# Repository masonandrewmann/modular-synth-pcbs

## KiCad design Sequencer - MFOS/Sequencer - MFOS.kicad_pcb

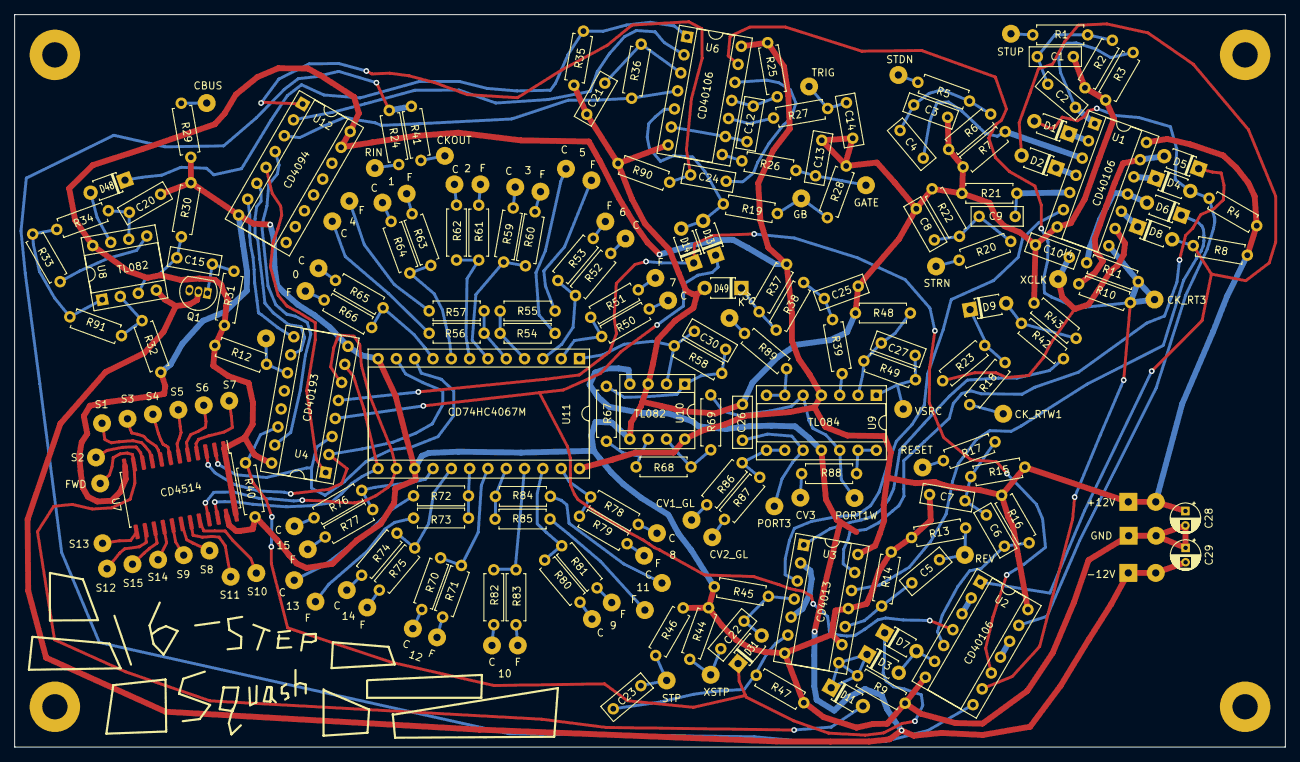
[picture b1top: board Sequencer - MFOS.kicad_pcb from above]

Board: 2 copper layers, 176.3 x 101.6 mm, 219 parts (0 on the bottom side), 162 nets.

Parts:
C1, C3, C7, C8, C22, C23: 0.01uF; C_Rect_L7.0mm_W2.5mm_P5.00mm
C2, C4, C5, C6, C9: 0.02uF; C_Rect_L7.0mm_W2.5mm_P5.00mm
C10: 1uF; C_Rect_L7.0mm_W2.5mm_P5.00mm
C12, C13, C14, C21: 0.001u; C_Rect_L7.0mm_W2.5mm_P5.00mm
C15, C20: 0.01u; C_Rect_L7.0mm_W2.5mm_P5.00mm
C24: 100p; C_Rect_L7.0mm_W2.5mm_P5.00mm
C25, C26: 0.1u; C_Rect_L7.0mm_W2.5mm_P5.00mm
C27, C30: 470p; C_Rect_L7.0mm_W2.5mm_P5.00mm
C28, C29: 100u; CP_Radial_D4.0mm_P2.00mm
D1, D2, D3, D4, D5, D6, D7, D8, D9, D11, D13, D14, D31, D48: D; D_T-1_P5.08mm_Horizontal
D49: D_Zener; D_T-1_P5.08mm_Horizontal
J1: STUP; SolderWirePad_1x01_Drill1mm
J2: STDN; SolderWirePad_1x01_Drill1mm
J3: XSTP; SolderWirePad_1x01_Drill1mm
J4: XCLK; SolderWirePad_1x01_Drill1mm
J5: CKOUT; SolderWirePad_1x01_Drill1mm
J6: GATE; SolderWirePad_1x01_Drill1mm
J7: TRIG; SolderWirePad_1x01_Drill1mm
J8: GB; SolderWirePad_1x01_Drill1mm
J9: CBUS; SolderWirePad_1x01_Drill1mm
J10: S7; SolderWirePad_1x01_Drill1mm
J11: S6; SolderWirePad_1x01_Drill1mm
J12: S5; SolderWirePad_1x01_Drill1mm
J13: S4; SolderWirePad_1x01_Drill1mm
J14: S3; SolderWirePad_1x01_Drill1mm
J15: S2; SolderWirePad_1x01_Drill1mm
J16: S1; SolderWirePad_1x01_Drill1mm
J17: S0; SolderWirePad_1x01_Drill1mm
J18: S8; SolderWirePad_1x01_Drill1mm
J19: S9; SolderWirePad_1x01_Drill1mm
J20: S10; SolderWirePad_1x01_Drill1mm
J21: S11; SolderWirePad_1x01_Drill1mm
J22: RIN; SolderWirePad_1x01_Drill1mm
J23: S12; SolderWirePad_1x01_Drill1mm
J24: S13; SolderWirePad_1x01_Drill1mm
J25: S14; SolderWirePad_1x01_Drill1mm
J26: S15; SolderWirePad_1x01_Drill1mm
J27: CV1_GL; SolderWirePad_1x01_Drill1mm
J28: CV2_GL; SolderWirePad_1x01_Drill1mm
J29: CV3; SolderWirePad_1x01_Drill1mm
J30: CV4; SolderWirePad_1x01_Drill1mm
J31: 7C; SolderWirePad_1x01_Drill1mm
J32: 7F; SolderWirePad_1x01_Drill1mm
J33: 6C; SolderWirePad_1x01_Drill1mm
J34: 6F; SolderWirePad_1x01_Drill1mm
J35: 5C; SolderWirePad_1x01_Drill1mm
J36: 5F; SolderWirePad_1x01_Drill1mm
J37: 4C; SolderWirePad_1x01_Drill1mm
J38: 4F; SolderWirePad_1x01_Drill1mm
J39: 3C; SolderWirePad_1x01_Drill1mm
J40: 3F; SolderWirePad_1x01_Drill1mm
J41: 2C; SolderWirePad_1x01_Drill1mm
J42: 2F; SolderWirePad_1x01_Drill1mm
J43: 1C; SolderWirePad_1x01_Drill1mm
J44: 1F; SolderWirePad_1x01_Drill1mm
J45: 0C; SolderWirePad_1x01_Drill1mm
J46: 0F; SolderWirePad_1x01_Drill1mm
J47: 12C; SolderWirePad_1x01_Drill1mm
J48: 12F; SolderWirePad_1x01_Drill1mm
J49: 13C; SolderWirePad_1x01_Drill1mm
J50: 13F; SolderWirePad_1x01_Drill1mm
J51: 14C; SolderWirePad_1x01_Drill1mm
J52: 14F; SolderWirePad_1x01_Drill1mm
J53: 15C; SolderWirePad_1x01_Drill1mm
J54: 15F; SolderWirePad_1x01_Drill1mm
J55: 8C; SolderWirePad_1x01_Drill1mm
J56: 8F; SolderWirePad_1x01_Drill1mm
J57: 9C; SolderWirePad_1x01_Drill1mm
J58: 9F; SolderWirePad_1x01_Drill1mm
J59: 10C; SolderWirePad_1x01_Drill1mm
J60: 10F; SolderWirePad_1x01_Drill1mm
J61: 11C; SolderWirePad_1x01_Drill1mm
J62: 11F; SolderWirePad_1x01_Drill1mm
J63: CK_RT1W; SolderWirePad_1x01_Drill1mm
J64: CK_RT3; SolderWirePad_1x01_Drill1mm
J65: STRN; SolderWirePad_1x01_Drill1mm
J66: REV; SolderWirePad_1x01_Drill1mm
J67: STP; SolderWirePad_1x01_Drill1mm
J68: RESET; SolderWirePad_1x01_Drill1mm
J69: RAND; SolderWirePad_1x01_Drill1mm
J70: PORT1W; SolderWirePad_1x01_Drill1mm
J71: PORT3; SolderWirePad_1x01_Drill1mm
J72: VSRC; SolderWirePad_1x01_Drill1mm
J73: +12V_Conn; SolderWirePad_1x02_P3.81mm_Drill1mm
J74: GND_Conn; SolderWirePad_1x02_P3.81mm_Drill1mm
J75: -12V_Conn; SolderWirePad_1x02_P3.81mm_Drill1mm
Q1: 2N3904; TO-92_Inline
R1, R5, R10, R11, R17, R20, R90: 10K; R_Axial_DIN0207_L6.3mm_D2.5mm_P7.62mm_Horizontal
R2, R6, R15, R22: 680K; R_Axial_DIN0207_L6.3mm_D2.5mm_P7.62mm_Horizontal
R3, R7, R16, R21: 220K; R_Axial_DIN0207_L6.3mm_D2.5mm_P7.62mm_Horizontal
R4, R8, R12, R40: 47K; R_Axial_DIN0207_L6.3mm_D2.5mm_P7.62mm_Horizontal
R9, R19, R33, R44, R45, R46, R47, R50, R52, R54, R56, R59, R61, R63, R65, R70, R72, R74, R76, R78, R80, R82, R84: 100K; R_Axial_DIN0207_L6.3mm_D2.5mm_P7.62mm_Horizontal
R13, R14, R34, R36: 1M; R_Axial_DIN0207_L6.3mm_D2.5mm_P7.62mm_Horizontal
R18: 20K; R_Axial_DIN0207_L6.3mm_D2.5mm_P7.62mm_Horizontal
R23: 6.2K; R_Axial_DIN0207_L6.3mm_D2.5mm_P7.62mm_Horizontal
R24: 3K; R_Axial_DIN0207_L6.3mm_D2.5mm_P7.62mm_Horizontal
R25, R48, R58: 100k; R_Axial_DIN0207_L6.3mm_D2.5mm_P7.62mm_Horizontal
R26, R27, R86, R87, R88, R89: 1k; R_Axial_DIN0207_L6.3mm_D2.5mm_P7.62mm_Horizontal
R28, R32, R35: 4k7; R_Axial_DIN0207_L6.3mm_D2.5mm_P7.62mm_Horizontal
R29: 3k; R_Axial_DIN0207_L6.3mm_D2.5mm_P7.62mm_Horizontal
R30, R31, R51, R53, R55, R57, R60, R62, R64, R66, R71, R73, R75, R77, R79, R81, R83, R85: 2M; R_Axial_DIN0207_L6.3mm_D2.5mm_P7.62mm_Horizontal
R37, R67, R68: 10k; R_Axial_DIN0207_L6.3mm_D2.5mm_P7.62mm_Horizontal
R38, R39: 47k; R_Axial_DIN0207_L6.3mm_D2.5mm_P7.62mm_Horizontal
R41, R42: 1K; R_Axial_DIN0207_L6.3mm_D2.5mm_P7.62mm_Horizontal
R43: 3.9K; R_Axial_DIN0207_L6.3mm_D2.5mm_P7.62mm_Horizontal
R49: 200k; R_Axial_DIN0207_L6.3mm_D2.5mm_P7.62mm_Horizontal
R69: 22; R_Axial_DIN0207_L6.3mm_D2.5mm_P7.62mm_Horizontal
R91: 4M7; R_Axial_DIN0207_L6.3mm_D2.5mm_P7.62mm_Horizontal
U1, U2, U6: 40106; DIP-14_W7.62mm_Socket
U3: 4013; DIP-14_W7.62mm_Socket
U4: 40193; DIP-16_W7.62mm_Socket
U7: 4514; SOIC-24W_7.5x15.4mm_P1.27mm
U8, U10: TL082; DIP-8_W7.62mm_Socket
U9: TL084; DIP-14_W7.62mm_Socket
U11: CD74HC4067M; DIP-24_W15.24mm_Socket
U12: CD4094; DIP-16_W7.62mm_Socket
e: MountingHole_3.5mm_Pad

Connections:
+12V: C28.1, J73.1, J73.2, R4.2, R8.2, R12.1, R15.2, R16.1, R25.2, R31.1, R37.2, U1.14, U2.14, U3.14, U4.16, U6.14, U7.1, U7.24, U8.8, U9.4, U10.8, U11.24, U12.15, U12.16
-12V: C29.2, J75.1, J75.2, Q1.2, U8.4, U9.11, U10.4
CLK: J64.1, R10.2, R11.2, U1.8, U2.9, U6.13
CLR: D7.1, D31.1, R40.1, U4.14
DA: U4.15, U12.4
DB: U4.1, U12.5
DC: U4.10, U12.6
DD: U4.9, U12.7
DN: D13.1, U2.4, U4.4
Earth: C1.2, C3.2, C7.2, C8.1, C10.2, C13.2, C14.2, C20.1, C21.1, C25.1, C26.2, C28.2, C29.1, D49.2, J74.1, J74.2, R2.1, R3.1, R6.1, R7.1, R9.1, R13.1, R14.1, R21.2, R22.2, R28.1, R29.1, R30.2, R32.2, R35.2, R40.2, R43.2, R44.2, R45.1, R46.2, R47.1, R48.1, R90.2, U1.7, U2.7, U3.7, U3.9, U3.11, U4.8, U6.7, U7.12, U7.23, U10.3, U10.5, U11.12, U11.15, U12.8
FWD: D11.2, J17.1, U7.11
unnamed: C1.1, C2.2, R1.1, R2.2
unnamed: C2.1, R3.2, U1.1
unnamed: C3.1, C4.2, R5.1, R6.2
unnamed: C4.1, R7.2, U1.3
unnamed: C5.1, R14.2, U3.10
unnamed: C6.1, R16.2, U2.5
unnamed: C6.2, C7.1, R15.1, R17.2
unnamed: C8.2, C9.2, R20.2, R22.1
unnamed: C9.1, R21.1, U1.5
unnamed: C10.1, J4.1, R23.2, U1.9
unnamed: C12.1, R25.1, U6.11
unnamed: C12.2, U6.6, U6.9
unnamed: C13.1, J6.1, R26.1
unnamed: C14.1, J7.1, R27.1
unnamed: C15.1, R30.1, U8.3
unnamed: C15.2, Q1.1, R31.2
unnamed: C20.2, R34.1, U8.6
unnamed: C21.2, R36.2, U6.3
unnamed: C22.1, D31.2, R45.2, U3.4
unnamed: C22.2, J3.1, R44.1
unnamed: C23.1, R47.2, U3.6
unnamed: C24.1, U6.12
unnamed: C24.2, R90.1, U12.1
unnamed: C25.2, R38.1, R39.2
unnamed: C26.1, J71.1, U9.10
unnamed: C27.1, J72.1, R49.1, U9.1
unnamed: C27.2, R48.2, R49.2, U9.2
unnamed: C30.1, R58.1, R67.2, U10.1
unnamed: C30.2, R58.2, U10.2, U11.1
unnamed: D1.1, U1.2
unnamed: D1.2, D5.2, R4.1, U2.13
unnamed: D2.1, U1.4
unnamed: D2.2, D6.2, R8.1, U2.1
unnamed: D4.1, U3.13
unnamed: D4.2, R10.1, U1.13
unnamed: D5.1, U1.12
unnamed: D6.1, U1.10
unnamed: D8.1, U3.12
unnamed: D8.2, R11.1, U1.11
unnamed: D9.1, R18.2, R23.1
unnamed: D9.2, R42.2, R43.1
unnamed: J22.1, R24.1
unnamed: D3.1, D11.1, R9.2, U3.8
unnamed: D13.2, D14.2, R19.2, U6.5
unnamed: J9.1, R29.2
unnamed: J10.1, U7.4
unnamed: J11.1, U7.5
unnamed: J12.1, U7.6
unnamed: J13.1, U7.7
unnamed: J14.1, U7.8
unnamed: J15.1, U7.10
unnamed: J16.1, U7.9
unnamed: J18.1, U7.18
unnamed: J19.1, U7.17
unnamed: J20.1, U7.20
unnamed: J21.1, U7.19
unnamed: J23.1, U7.14
unnamed: J24.1, U7.13
unnamed: J25.1, U7.16
unnamed: J26.1, U7.15
unnamed: D48.1, R35.1, U6.1
unnamed: D48.2, U8.7
unnamed: D49.1, R37.1, R38.2
unnamed: J1.1, R1.2
unnamed: J2.1, R5.2
unnamed: J5.1, R41.1
unnamed: J8.1, R19.1, R28.2
unnamed: J27.1, R86.1
unnamed: J28.1, R87.1
unnamed: J29.1, R88.1
unnamed: J30.1, R89.1
unnamed: J31.1, R50.2
unnamed: J32.1, R51.2
unnamed: J33.1, R52.2
unnamed: J34.1, R53.2
unnamed: J35.1, R54.2
unnamed: J36.1, R55.2
unnamed: J37.1, R56.2
unnamed: J38.1, R57.2
unnamed: J39.1, R59.2
unnamed: J40.1, R60.2
unnamed: J41.1, R61.2
unnamed: J42.1, R62.2
unnamed: J43.1, R63.2
unnamed: J44.1, R64.2
unnamed: J45.1, R65.2
unnamed: J46.1, R66.2
unnamed: J47.1, R70.2
unnamed: J48.1, R71.2
unnamed: J49.1, R72.2
unnamed: J50.1, R73.2
unnamed: J51.1, R74.2
unnamed: J52.1, R75.2
unnamed: J53.1, R76.2
unnamed: J54.1, R77.2
unnamed: J55.1, R78.2
unnamed: J56.1, R79.2
unnamed: J57.1, R80.2
unnamed: J58.1, R81.2
unnamed: J59.1, R82.2
unnamed: J60.1, R83.2
unnamed: J61.1, R84.2
unnamed: J62.1, R85.2
unnamed: J63.1, R18.1
unnamed: J65.1, R20.1
unnamed: J68.1, R17.1
unnamed: J70.1, R69.1, U9.5, U9.12
unnamed: R24.2, R41.2, U2.8
unnamed: R26.2, U6.8
unnamed: R27.2, U6.10
unnamed: R32.1, R91.2, U8.2
unnamed: R33.1, U8.5
unnamed: R33.2, R34.2, R91.1, U8.1
unnamed: R36.1, U6.4, U12.3
unnamed: R39.1, U9.3
unnamed: R42.1, U3.1
unnamed: R50.1, R51.1, U11.2
unnamed: R52.1, R53.1, U11.3
unnamed: R54.1, R55.1, U11.4
unnamed: R56.1, R57.1, U11.5
unnamed: R59.1, R60.1, U11.6
unnamed: R61.1, R62.1, U11.7
unnamed: R63.1, R64.1, U11.8
unnamed: R65.1, R66.1, U11.9
unnamed: R67.1, R68.2, U10.6
unnamed: R68.1, R69.2, U10.7
unnamed: R70.1, R71.1, U11.19
unnamed: R72.1, R73.1, U11.18
unnamed: R74.1, R75.1, U11.17
unnamed: R76.1, R77.1, U11.16
unnamed: R78.1, R79.1, U11.23
unnamed: R80.1, R81.1, U11.22
unnamed: R82.1, R83.1, U11.21
unnamed: R84.1, R85.1, U11.20
unnamed: R86.2, R87.2, U9.8, U9.9
unnamed: R88.2, U9.13, U9.14
unnamed: R89.2, U9.6, U9.7
unnamed: U1.6, U3.3
unnamed: U2.2, U2.3
unnamed: U2.11, U2.12
unnamed: U3.2, U3.5
unnamed: U6.2, U12.2
QA: U4.3, U7.2, U11.10
QB: U4.2, U7.3, U11.11
QC: U4.6, U7.21, U11.14
QD: U4.7, U7.22, U11.13
REV: C5.2, J66.1, R13.2
RND: J69.1, R12.2, U4.11
RST: D3.2, D7.2, U2.6
STP: C23.2, J67.1, R46.1
UP: D14.1, U2.10, U4.5

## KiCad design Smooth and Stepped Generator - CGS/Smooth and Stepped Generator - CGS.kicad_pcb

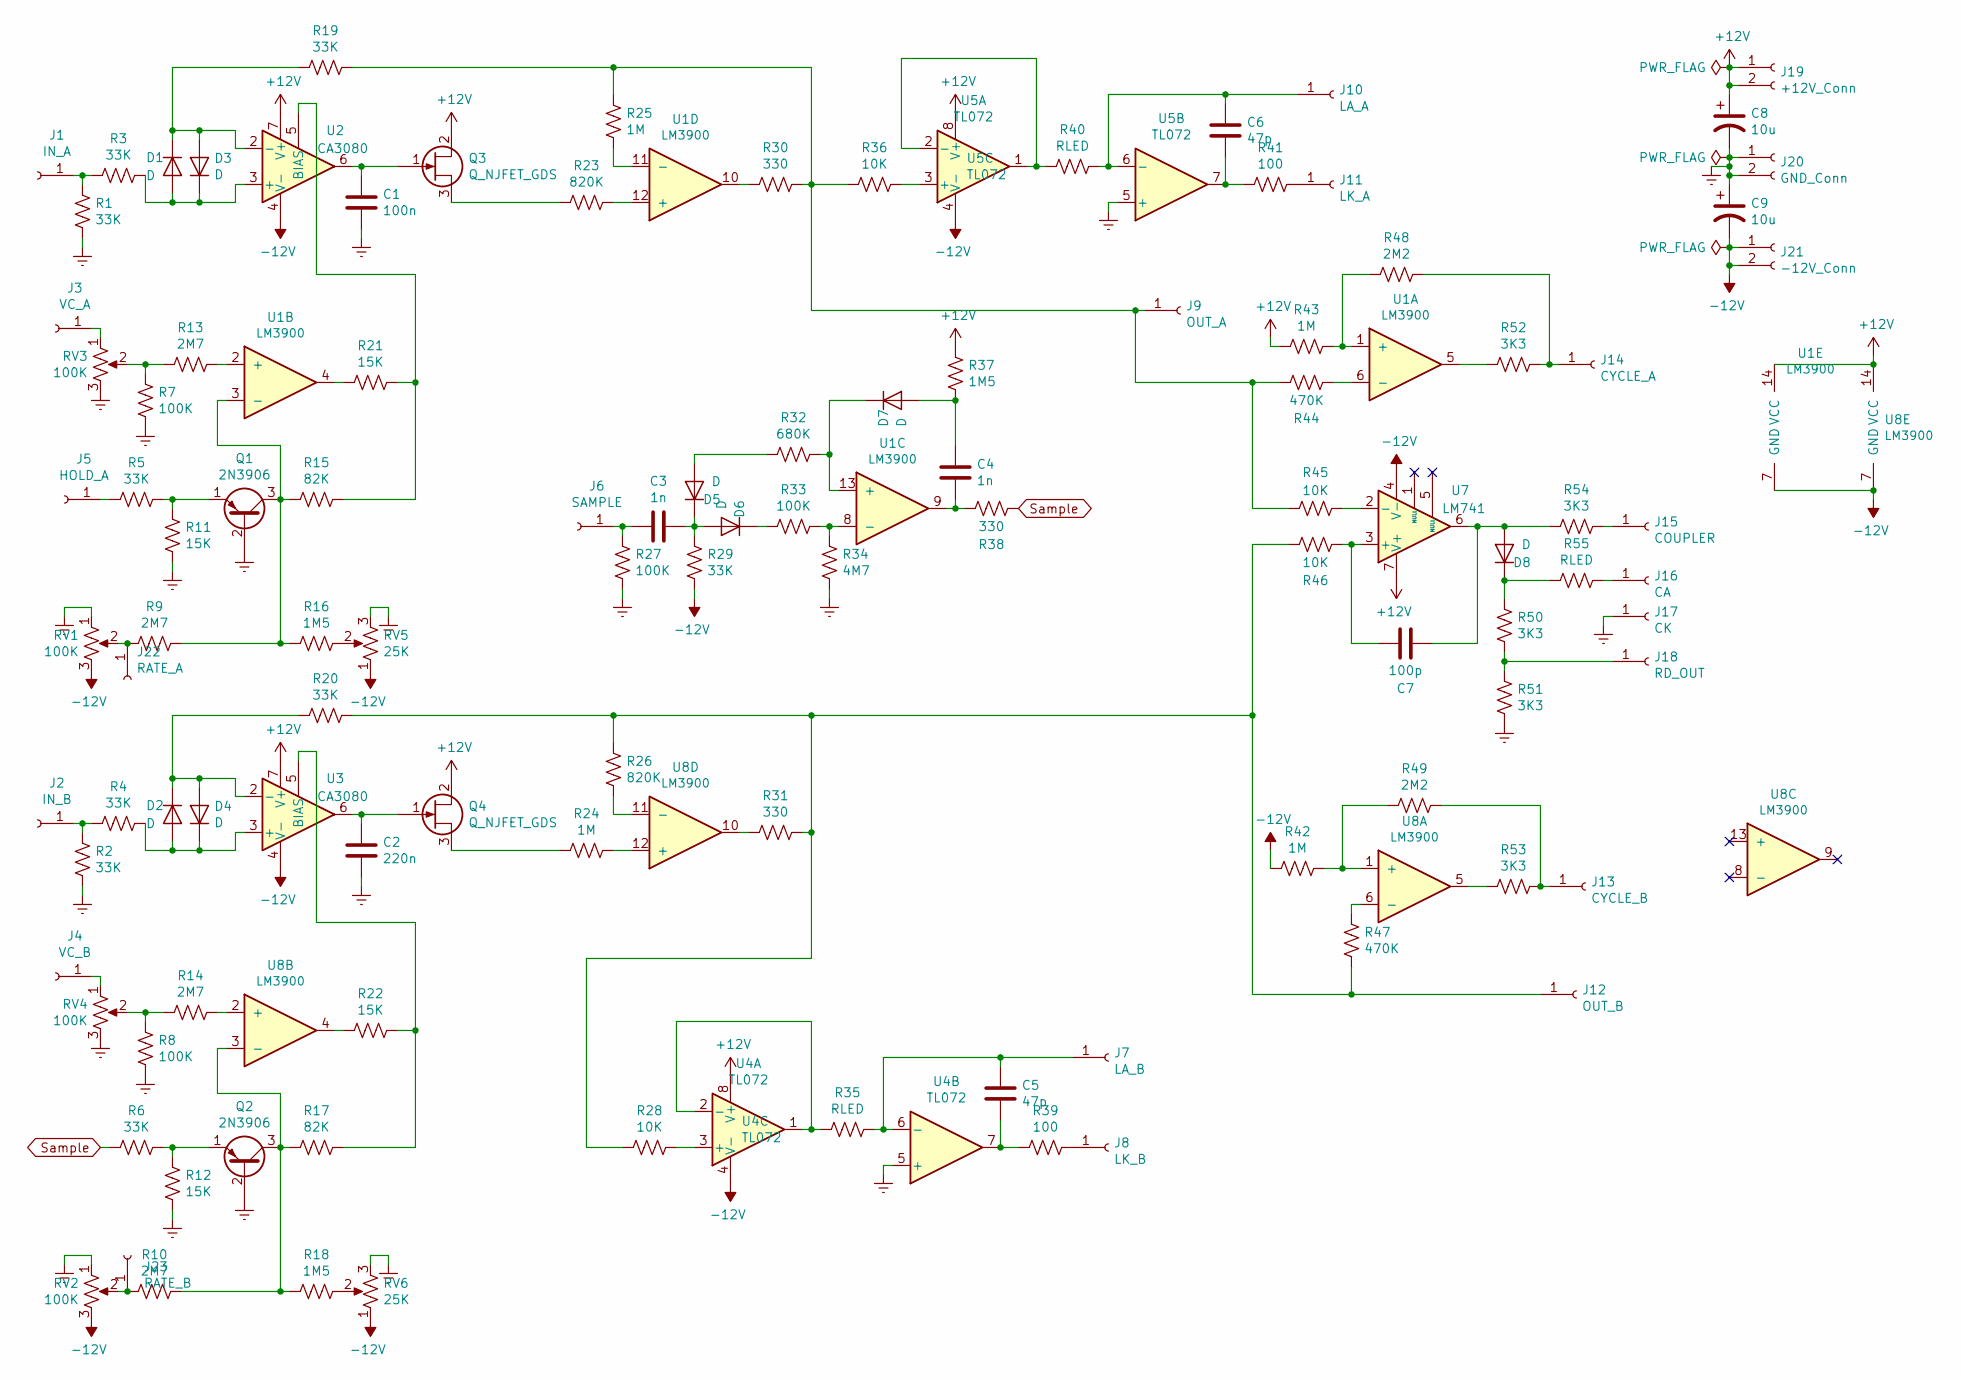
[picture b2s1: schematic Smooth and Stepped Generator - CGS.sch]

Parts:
C1: 100n; C_Rect_L7.0mm_W2.5mm_P5.00mm
C2: 220n; C_Rect_L7.0mm_W2.5mm_P5.00mm
C3, C4: 1n; C_Rect_L7.0mm_W2.5mm_P5.00mm
C5, C6: 47p; C_Rect_L7.0mm_W2.5mm_P5.00mm
C7: 100p; C_Rect_L7.0mm_W2.5mm_P5.00mm
C8, C9: 10u; CP_Radial_D4.0mm_P2.00mm
D1, D2, D3, D4, D5, D6, D7: D; D_T-1_P5.08mm_Horizontal
D8: D; SolderWirePad_1x01_Drill1mm
J1: IN_A; SolderWirePad_1x01_Drill1mm
J2: IN_B; SolderWirePad_1x01_Drill1mm
J3: VC_A; SolderWirePad_1x01_Drill1mm
J4: VC_B; SolderWirePad_1x01_Drill1mm
J5: HOLD_A; SolderWirePad_1x01_Drill1mm
J6: SAMPLE; SolderWirePad_1x01_Drill1mm
J7: LA_B; SolderWirePad_1x01_Drill1mm
J8: LK_B; SolderWirePad_1x01_Drill1mm
J9: OUT_A; SolderWirePad_1x01_Drill1mm
J10: LA_A; SolderWirePad_1x01_Drill1mm
J11: LK_A; SolderWirePad_1x01_Drill1mm
J12: OUT_B; SolderWirePad_1x01_Drill1mm
J13: CYCLE_B; SolderWirePad_1x01_Drill1mm
J14: CYCLE_A; SolderWirePad_1x01_Drill1mm
J15: COUPLER; SolderWirePad_1x01_Drill1mm
J16: CA; SolderWirePad_1x01_Drill1mm
J17: CK; SolderWirePad_1x01_Drill1mm
J18: RD_OUT; SolderWirePad_1x02_P3.81mm_Drill1mm
J19: +12V_Conn; SolderWirePad_1x02_P3.81mm_Drill1mm
J20: GND_Conn; SolderWirePad_1x02_P3.81mm_Drill1mm
J21: -12V_Conn; SolderWirePad_1x02_P3.81mm_Drill1mm
J22: RATE_A; SolderWirePad_1x01_Drill1mm
J23: RATE_B; SolderWirePad_1x01_Drill1mm
Q1, Q2: 2N3906; TO-92_Inline
Q3, Q4: Q_NJFET_GDS; TO-92_Inline_Wide
R1, R2, R3, R4, R5, R6, R19, R20, R29: 33K; R_Axial_DIN0207_L6.3mm_D2.5mm_P7.62mm_Horizontal
R7, R8, R27, R33: 100K; R_Axial_DIN0207_L6.3mm_D2.5mm_P7.62mm_Horizontal
R9, R10, R13, R14: 2M7; R_Axial_DIN0207_L6.3mm_D2.5mm_P7.62mm_Horizontal
R11, R12, R21, R22: 15K; R_Axial_DIN0207_L6.3mm_D2.5mm_P7.62mm_Horizontal
R15, R17: 82K; R_Axial_DIN0207_L6.3mm_D2.5mm_P7.62mm_Horizontal
R16, R18, R37: 1M5; R_Axial_DIN0207_L6.3mm_D2.5mm_P7.62mm_Horizontal
R23, R26: 820K; R_Axial_DIN0207_L6.3mm_D2.5mm_P7.62mm_Horizontal
R24, R25, R42, R43: 1M; R_Axial_DIN0207_L6.3mm_D2.5mm_P7.62mm_Horizontal
R28, R36, R45, R46: 10K; R_Axial_DIN0207_L6.3mm_D2.5mm_P7.62mm_Horizontal
R30, R31, R38: 330; R_Axial_DIN0207_L6.3mm_D2.5mm_P7.62mm_Horizontal
R32: 680K; R_Axial_DIN0207_L6.3mm_D2.5mm_P7.62mm_Horizontal
R34: 4M7; R_Axial_DIN0207_L6.3mm_D2.5mm_P7.62mm_Horizontal
R35, R40, R55: RLED; R_Axial_DIN0207_L6.3mm_D2.5mm_P7.62mm_Horizontal
R39, R41: 100; R_Axial_DIN0207_L6.3mm_D2.5mm_P7.62mm_Horizontal
R44, R47: 470K; R_Axial_DIN0207_L6.3mm_D2.5mm_P7.62mm_Horizontal
R48, R49: 2M2; R_Axial_DIN0207_L6.3mm_D2.5mm_P7.62mm_Horizontal
R50, R51, R52, R53, R54: 3K3; R_Axial_DIN0207_L6.3mm_D2.5mm_P7.62mm_Horizontal
RV1, RV2, RV3, RV4: 100K
RV5, RV6: 25K; Potentiometer_Runtron_RM-065_Vertical
U1, U8: LM3900; DIP-14_W7.62mm_Socket
U2, U3: CA3080; DIP-8_W7.62mm_Socket
U4, U5: TL072; DIP-8_W7.62mm_Socket
U7: LM741; DIP-8_W7.62mm_Socket

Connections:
+12V: C8.1, J19.1, J19.2, Q3.2 (D), Q4.2 (D), R37.2, R43.2, U1.14 (VCC), U2.7 (V+), U3.7 (V+), U4.8 (V+), U5.8 (V+), U7.7 (V+), U8.14 (VCC)
-12V: C9.2, J21.1, J21.2, R29.2, R42.2, RV1.3, RV2.3, RV5.1, RV6.1, U1.7 (GND), U2.4 (V-), U3.4 (V-), U4.4 (V-), U5.4 (V-), U7.4 (V-), U8.7 (GND)
Earth: C1.2, C2.2, C8.2, C9.1, J17.1, J20.1, J20.2, Q1.2 (B), Q2.2 (B), R1.2, R2.2, R7.2, R8.2, R11.2, R12.2, R27.2, R34.1, R51.1, RV1.1, RV2.1, RV3.3, RV4.3, RV5.3, RV6.3, U4.5 (+), U5.5 (+)
unnamed: C1.1, Q3.1 (G), U2.6
unnamed: C2.1, Q4.1 (G), U3.6
unnamed: C3.1, J6.1, R27.1
unnamed: C3.2, D5.1 (K), D6.2 (A), R29.1
unnamed: C4.1, D7.2 (A), R37.1
unnamed: C4.2, R38.2, U1.9
unnamed: C5.1, J7.1, R35.1, U4.6 (-)
unnamed: C5.2, R39.2, U4.7
unnamed: C6.1, J10.1, R40.1, U5.6 (-)
unnamed: C6.2, R41.2, U5.7
unnamed: C7.1, D8.2 (A), R54.2, U7.6
unnamed: C7.2, R46.1, U7.3 (+)
unnamed: D1.1 (K), D3.2 (A), R19.2, U2.2 (-)
unnamed: D1.2 (A), D3.1 (K), R3.1, U2.3 (+)
unnamed: D2.1 (K), D4.2 (A), R20.2, U3.2 (-)
unnamed: D2.2 (A), D4.1 (K), R4.1, U3.3 (+)
unnamed: D5.2 (A), R32.2
unnamed: D6.1 (K), R33.2
unnamed: D7.1 (K), R32.1, U1.13 (+)
unnamed: D8.1 (K), R50.2, R55.2
unnamed: J1.1, R1.1, R3.2
unnamed: J2.1, R2.1, R4.2
unnamed: J5.1, R5.2
unnamed: J8.1, R39.1
unnamed: J9.1, R19.1, R25.2, R30.2, R36.2, R44.2, R45.2
unnamed: J11.1, R41.1
unnamed: J12.1, R20.1, R26.2, R28.2, R31.2, R46.2, R47.1
unnamed: J13.1, R49.1, R53.1
unnamed: J14.1, R48.1, R52.1
unnamed: J15.1, R54.1
unnamed: J16.1, R55.1
unnamed: J18.1, R50.1, R51.2
unnamed: J22.1, R9.2, RV1.2
unnamed: J23.1, R10.2, RV2.2
unnamed: Q1.1 (E), R5.1, R11.1
unnamed: Q1.3 (C), R9.1, R15.2, R16.2, U1.3 (-)
unnamed: Q2.1 (E), R6.1, R12.1
unnamed: Q2.3 (C), R10.1, R17.2, R18.2, U8.3 (-)
unnamed: Q3.3 (S), R23.1
unnamed: Q4.3 (S), R24.1
unnamed: R13.1, U1.2 (+)
unnamed: R14.1, U8.2 (+)
unnamed: R15.1, R21.1, U2.5 (BIAS)
unnamed: R16.1, RV5.2
unnamed: R17.1, R22.1, U3.5 (BIAS)
unnamed: R18.1, RV6.2
unnamed: R21.2, U1.4
unnamed: R22.2, U8.4
unnamed: R23.2, U1.12 (+)
unnamed: R24.2, U8.12 (+)
unnamed: R25.1, U1.11 (-)
unnamed: R26.1, U8.11 (-)
unnamed: R28.1, U4.3 (+)
unnamed: R30.1, U1.10
unnamed: R31.1, U8.10
unnamed: R33.1, R34.2, U1.8 (-)
unnamed: R35.2, U4.1, U4.2 (-)
unnamed: R36.1, U5.3 (+)
unnamed: R40.2, U5.1, U5.2 (-)
unnamed: R42.1, R49.2, U8.1 (+)
unnamed: R43.1, R48.2, U1.1 (+)
unnamed: R44.1, U1.6 (-)
unnamed: R45.1, U7.2 (-)
unnamed: R47.2, U8.6 (-)
unnamed: R52.2, U1.5
unnamed: R53.2, U8.5
Sample: R6.2, R38.1

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
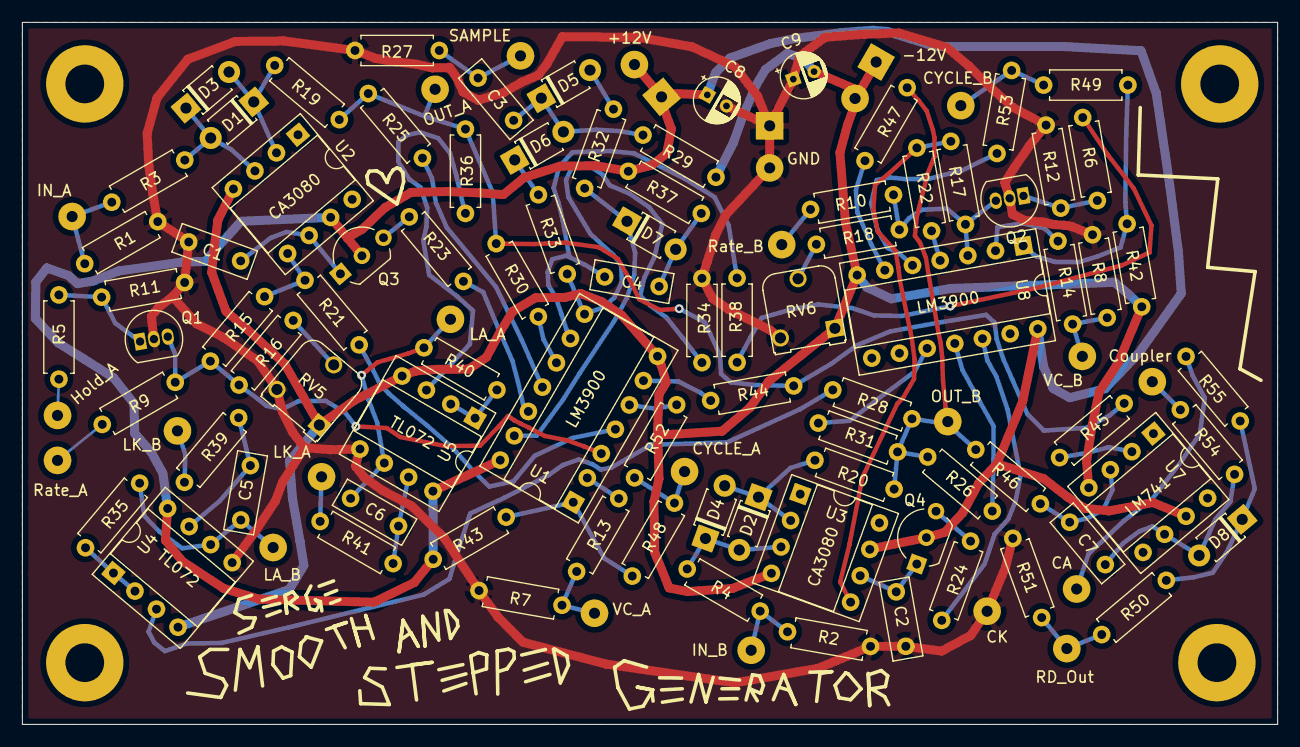
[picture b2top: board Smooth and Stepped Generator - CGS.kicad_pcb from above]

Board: 2 copper layers, 113.5 x 63.5 mm, 108 parts (0 on the bottom side), 72 nets.

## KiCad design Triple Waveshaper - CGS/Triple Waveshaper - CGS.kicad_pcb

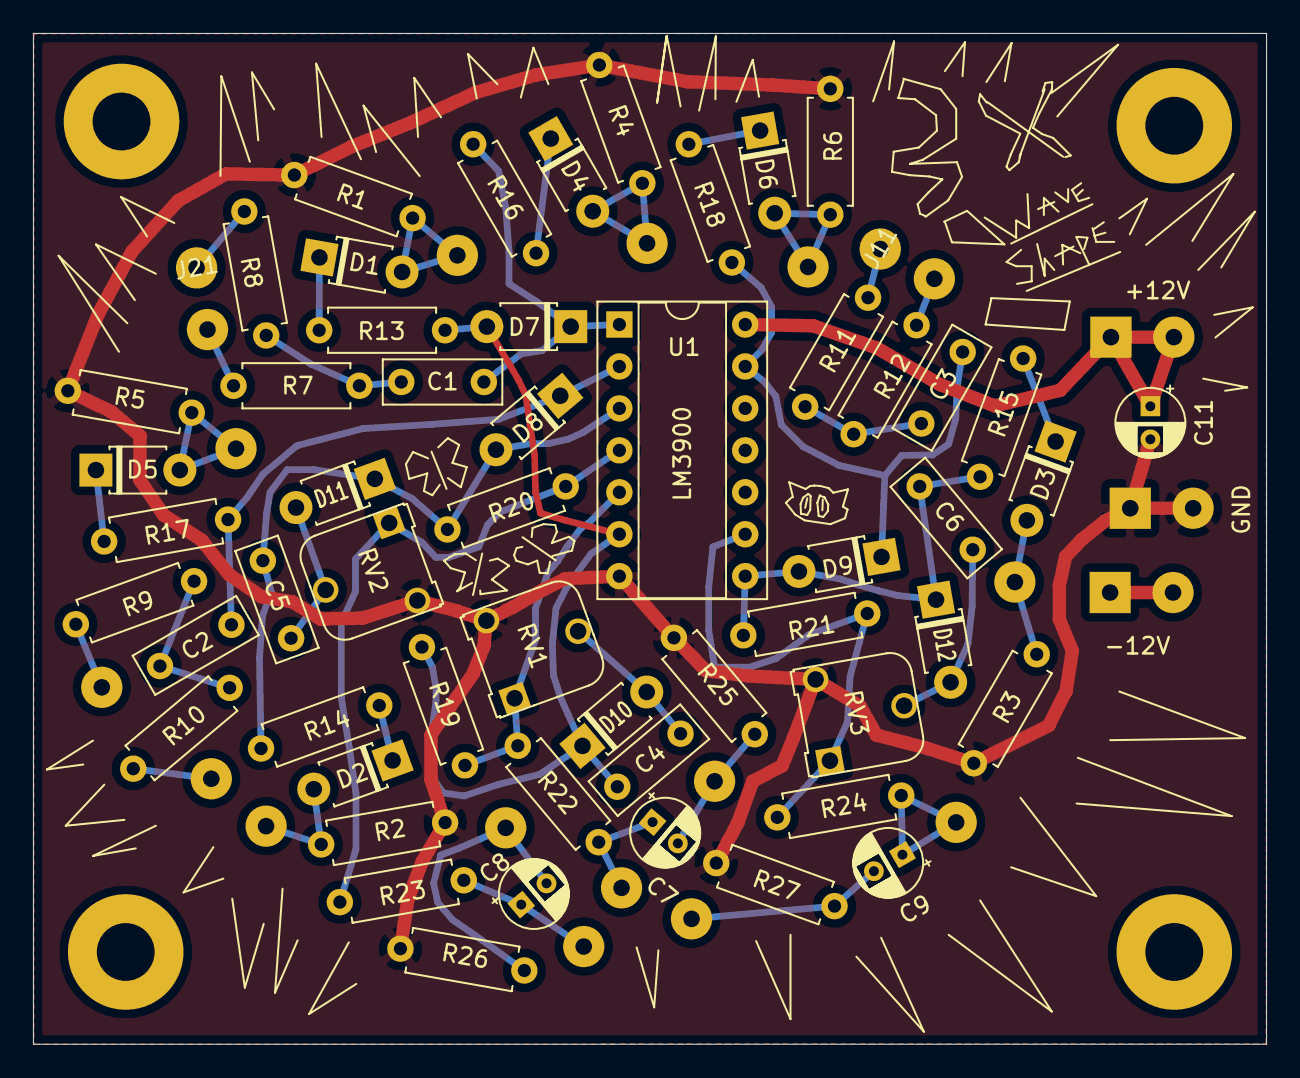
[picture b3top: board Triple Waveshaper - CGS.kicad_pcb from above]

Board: 2 copper layers, 74.7 x 61.2 mm, 74 parts (0 on the bottom side), 42 nets.

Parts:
C1, C2, C3: 470n; C_Rect_L7.0mm_W2.5mm_P5.00mm
C4, C5, C6: 100p; C_Rect_L7.0mm_W2.5mm_P5.00mm
C7, C8, C9: 47u; CP_Radial_D4.0mm_P2.00mm
C11: 10u; CP_Radial_D4.0mm_P2.00mm
D1, D2, D3, D4, D5, D6, D7, D8, D9, D10, D11, D12: 1N914; D_T-1_P5.08mm_Horizontal
J1: CV_1_A; SolderWirePad_1x01_Drill1mm
J2: CV_1_B; SolderWirePad_1x01_Drill1mm
J3: CV_1_C; SolderWirePad_1x01_Drill1mm
J4: CV_2_A; SolderWirePad_1x01_Drill1mm
J5: CV_2_B; SolderWirePad_1x01_Drill1mm
J6: CV_2_C; SolderWirePad_1x01_Drill1mm
J7: IN_A; SolderWirePad_1x01_Drill1mm
J8: Sum_In_B; SolderWirePad_1x01_Drill1mm
J9: IN_B; SolderWirePad_1x01_Drill1mm
J10: Sum_In_C; SolderWirePad_1x01_Drill1mm
J11: IN_C; SolderWirePad_1x01_Drill1mm
J12: DC_OUT_A; SolderWirePad_1x01_Drill1mm
J13: AC_OUT_A; SolderWirePad_1x01_Drill1mm
J14: DC_OUT_B; SolderWirePad_1x01_Drill1mm
J15: AC_OUT_B; SolderWirePad_1x01_Drill1mm
J16: DC_OUT_C; SolderWirePad_1x01_Drill1mm
J17: AC_OUT_C; SolderWirePad_1x01_Drill1mm
J18: +12V_Conn; SolderWirePad_1x02_P3.81mm_Drill1mm
J19: GND_Conn; SolderWirePad_1x02_P3.81mm_Drill1mm
J20: -12V_Conn; SolderWirePad_1x02_P3.81mm_Drill1mm
J21: AUX_In_A; SolderWirePad_1x01_Drill1mm
R1, R2, R3: 100K; R_Axial_DIN0207_L6.3mm_D2.5mm_P7.62mm_Horizontal
R4, R5, R6, R16, R17, R18: R_US; R_Axial_DIN0207_L6.3mm_D2.5mm_P7.62mm_Horizontal
R7, R8, R9, R10, R11, R12: 220k; R_Axial_DIN0207_L6.3mm_D2.5mm_P7.62mm_Horizontal
R13, R14, R15, R19, R20, R21: 1M5; R_Axial_DIN0207_L6.3mm_D2.5mm_P7.62mm_Horizontal
R22, R23, R24: 330; R_Axial_DIN0207_L6.3mm_D2.5mm_P7.62mm_Horizontal
R25, R26, R27: 150k; R_Axial_DIN0207_L6.3mm_D2.5mm_P7.62mm_Horizontal
RV1, RV2, RV3: 20k; Potentiometer_Runtron_RM-065_Vertical
U1: LM3900; DIP-14_W7.62mm_Socket

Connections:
+12V: C11.1, J18.1, J18.2, U1.14
-12V: J20.1, J20.2
Earth: C11.2, J19.1, J19.2, R1.1, R2.1, R3.1, R4.1, R5.1, R6.1, R25.1, R26.1, R27.1, RV1.3, RV2.3, RV3.3, U1.7
unnamed: C1.1, R7.1, R8.1
unnamed: C1.2, D7.1, R16.1, U1.1
unnamed: C2.1, R9.1, R10.1
unnamed: C2.2, D8.1, R17.1, U1.2
unnamed: C3.1, R11.1, R12.1
unnamed: C3.2, D9.1, R18.1, U1.13
unnamed: C4.1, D7.2, D10.1, R13.1, R19.2, U1.6
unnamed: C4.2, D10.2, RV1.2
unnamed: C5.1, D8.2, D11.1, R14.1, R20.2, U1.3
unnamed: C5.2, D11.2, RV2.2
unnamed: C6.1, D9.2, D12.1, R15.1, R21.2, U1.8
unnamed: C6.2, D12.2, RV3.2
unnamed: C7.1, J12.1, R22.1
unnamed: C7.2, J13.1, R25.2
unnamed: C8.1, J14.1, R23.1
unnamed: C8.2, J15.1, R26.2
unnamed: C9.1, J16.1, R24.1
unnamed: C9.2, J17.1, R27.2
unnamed: D1.1, R13.2
unnamed: D1.2, J1.1, R1.2
unnamed: D2.1, R14.2
unnamed: D2.2, J2.1, R2.2
unnamed: D3.1, R15.2
unnamed: D3.2, J3.1, R3.2
unnamed: D4.1, R16.2
unnamed: D4.2, J4.1, R4.2
unnamed: D5.1, R17.2
unnamed: D5.2, J5.1, R5.2
unnamed: D6.1, R18.2
unnamed: D6.2, J6.1, R6.2
unnamed: J7.1, R8.2
unnamed: J8.1, R9.2
unnamed: J9.1, R10.2
unnamed: J10.1, R11.2
unnamed: J11.1, R12.2
unnamed: J21.1, R7.2
unnamed: R19.1, R22.2, RV1.1, U1.5
unnamed: R20.1, R23.2, RV2.1, U1.4
unnamed: R21.1, R24.2, RV3.1, U1.9

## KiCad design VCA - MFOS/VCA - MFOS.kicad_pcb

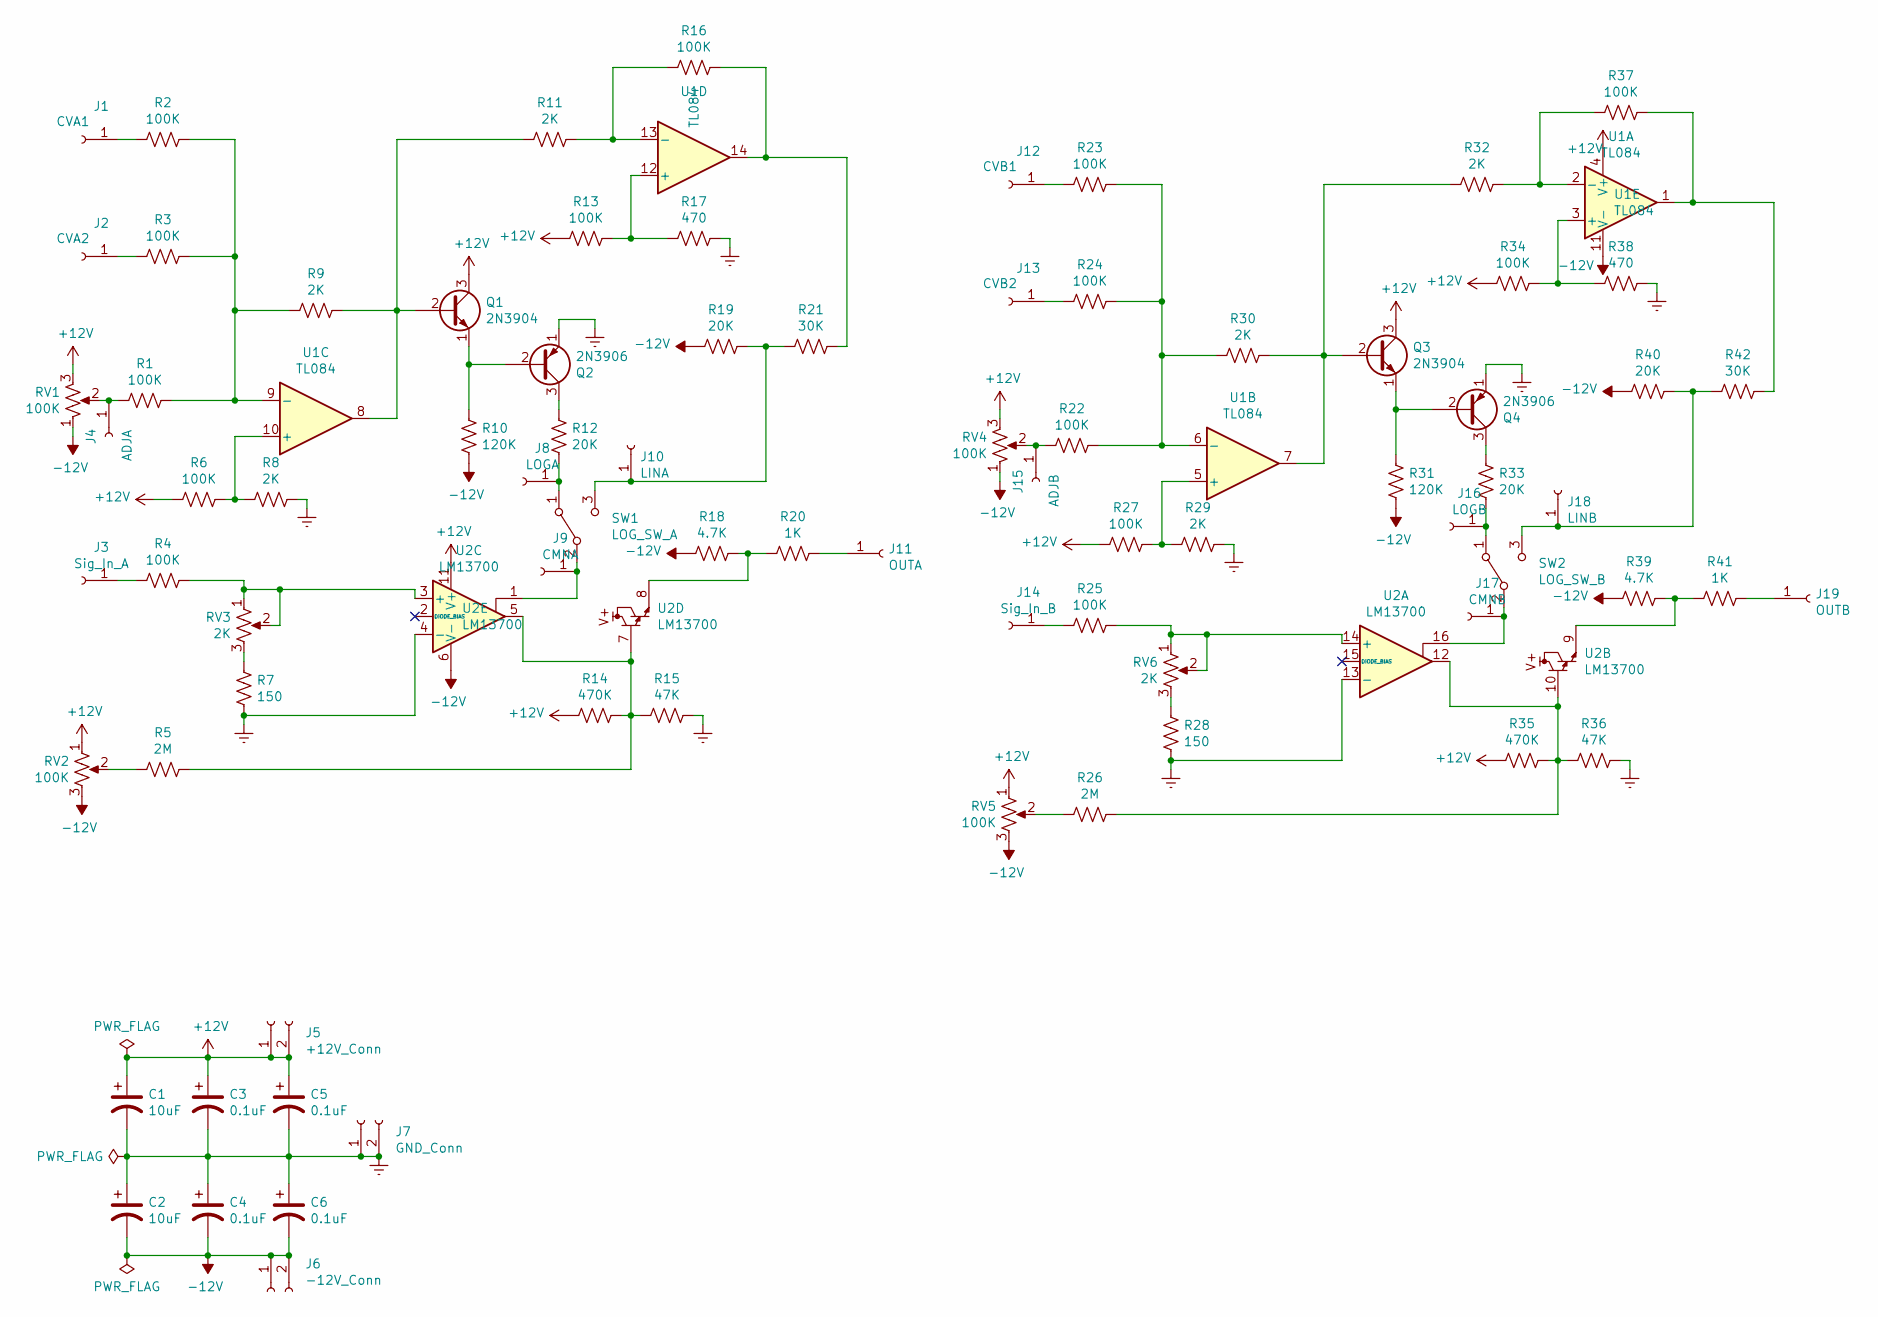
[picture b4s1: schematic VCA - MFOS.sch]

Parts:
C1, C2: 10uF; CP_Radial_D5.0mm_P2.50mm
C3, C4, C5, C6: 0.1uF; C_Rect_L7.0mm_W2.5mm_P5.00mm
J1: CVA1; SolderWirePad_1x01_Drill1mm
J2: CVA2; SolderWirePad_1x01_Drill1mm
J3: Sig_In_A; SolderWirePad_1x01_Drill1mm
J4: ADJA; SolderWirePad_1x01_Drill1mm
J5: +12V_Conn; SolderWirePad_1x02_P3.81mm_Drill1mm
J6: -12V_Conn; SolderWirePad_1x02_P3.81mm_Drill1mm
J7: GND_Conn; SolderWirePad_1x02_P3.81mm_Drill1mm
J8: LOGA; SolderWirePad_1x01_Drill1mm
J9: CMNA; SolderWirePad_1x01_Drill1mm
J10: LINA; SolderWirePad_1x01_Drill1mm
J11: OUTA; SolderWirePad_1x01_Drill1mm
J12: CVB1; SolderWirePad_1x01_Drill1mm
J13: CVB2; SolderWirePad_1x01_Drill1mm
J14: Sig_In_B; SolderWirePad_1x01_Drill1mm
J15: ADJB; SolderWirePad_1x01_Drill1mm
J16: LOGB; SolderWirePad_1x01_Drill1mm
J17: CMNB; SolderWirePad_1x01_Drill1mm
J18: LINB; SolderWirePad_1x01_Drill1mm
J19: OUTB; SolderWirePad_1x01_Drill1mm
Q1, Q3: 2N3904; TO-92_Inline_Wide
Q2, Q4: 2N3906; TO-92_Inline_Wide
R1, R2, R3, R4, R6, R13, R16, R22, R23, R24, R25, R27, R34, R37: 100K; R_Axial_DIN0207_L6.3mm_D2.5mm_P7.62mm_Horizontal
R5, R26: 2M; R_Axial_DIN0207_L6.3mm_D2.5mm_P7.62mm_Horizontal
R7, R28: 150; R_Axial_DIN0207_L6.3mm_D2.5mm_P7.62mm_Horizontal
R8, R9, R11, R29, R30, R32: 2K; R_Axial_DIN0207_L6.3mm_D2.5mm_P7.62mm_Horizontal
R10, R31: 120K; R_Axial_DIN0207_L6.3mm_D2.5mm_P7.62mm_Horizontal
R12, R19, R33, R40: 20K; R_Axial_DIN0207_L6.3mm_D2.5mm_P7.62mm_Horizontal
R14, R35: 470K; R_Axial_DIN0207_L6.3mm_D2.5mm_P7.62mm_Horizontal
R15, R36: 47K; R_Axial_DIN0207_L6.3mm_D2.5mm_P7.62mm_Horizontal
R17, R38: 470; R_Axial_DIN0207_L6.3mm_D2.5mm_P7.62mm_Horizontal
R18, R39: 4.7K; R_Axial_DIN0207_L6.3mm_D2.5mm_P7.62mm_Horizontal
R20, R41: 1K; R_Axial_DIN0207_L6.3mm_D2.5mm_P7.62mm_Horizontal
R21, R42: 30K; R_Axial_DIN0207_L6.3mm_D2.5mm_P7.62mm_Horizontal
RV1: 100K; SolderWirePad_1x03_P4.445mm_Drill1.5mm
RV2, RV5: 100K; Potentiometer_Runtron_RM-065_Vertical
RV3, RV6: 2K; Potentiometer_Runtron_RM-065_Vertical
RV4: 100K; SolderWirePad_1x03_P3.175mm_Drill1mm
SW1: LOG_SW_A; SolderWirePad_1x03_P3.175mm_Drill0.8mm
SW2: LOG_SW_B; SolderWirePad_1x03_P3.175mm_Drill0.8mm
U1: TL084; DIP-14_W7.62mm_Socket
U2: LM13700; DIP-16_W7.62mm_Socket

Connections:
+12V: C1.1, C3.1, C5.1, J5.1, J5.2, Q1.3 (C), Q3.3 (C), R6.2, R13.2, R14.2, R27.2, R34.2, R35.2, RV1.3, RV2.1, RV4.3, RV5.1, U1.4 (V+), U2.11 (V+)
-12V: C2.2, C4.2, C6.2, J6.1, J6.2, R10.2, R18.2, R19.2, R31.2, R39.2, R40.2, RV1.1, RV2.3, RV4.1, RV5.3, U1.11 (V-), U2.6 (V-)
Earth: C1.2, C2.1, C3.2, C4.1, C5.2, C6.1, J7.1, J7.2, Q2.1 (E), Q4.1 (E), R7.2, R8.1, R15.1, R17.1, R28.2, R29.1, R36.1, R38.1, U2.4 (-), U2.13 (-)
unnamed: J1.1, R2.2
unnamed: J2.1, R3.2
unnamed: J3.1, R4.2
unnamed: J4.1, R1.2, RV1.2
unnamed: J8.1, R12.2, SW1.1 (A)
unnamed: J9.1, SW1.2 (B), U2.1
unnamed: J10.1, R19.1, R21.2, SW1.3 (C)
unnamed: J11.1, R20.1
unnamed: J12.1, R23.2
unnamed: J13.1, R24.2
unnamed: J14.1, R25.2
unnamed: J15.1, R22.2, RV4.2
unnamed: J16.1, R33.2, SW2.1 (A)
unnamed: J17.1, SW2.2 (B), U2.16
unnamed: J18.1, R40.1, R42.2, SW2.3 (C)
unnamed: J19.1, R41.1
unnamed: Q1.1 (E), Q2.2 (B), R10.1
unnamed: Q1.2 (B), R9.1, R11.2, U1.8
unnamed: Q2.3 (C), R12.1
unnamed: Q3.1 (E), Q4.2 (B), R31.1
unnamed: Q3.2 (B), R30.1, R32.2, U1.7
unnamed: Q4.3 (C), R33.1
unnamed: R1.1, R2.1, R3.1, R9.2, U1.9 (-)
unnamed: R4.1, RV3.1, RV3.2, U2.3 (+)
unnamed: R5.2, RV2.2
unnamed: R6.1, R8.2, U1.10 (+)
unnamed: R7.1, RV3.3
unnamed: R11.1, R16.2, U1.13 (-)
unnamed: R13.1, R17.2, U1.12 (+)
unnamed: R5.1, R14.1, R15.2, U2.5, U2.7
unnamed: R16.1, R21.1, U1.14
unnamed: R18.1, R20.2, U2.8
unnamed: R22.1, R23.1, R24.1, R30.2, U1.6 (-)
unnamed: R25.1, RV6.1, RV6.2, U2.14 (+)
unnamed: R26.1, R35.1, R36.2, U2.10, U2.12
unnamed: R26.2, RV5.2
unnamed: R27.1, R29.2, U1.5 (+)
unnamed: R28.1, RV6.3
unnamed: R32.1, R37.2, U1.2 (-)
unnamed: R34.1, R38.2, U1.3 (+)
unnamed: R37.1, R42.1, U1.1
unnamed: R39.1, R41.2, U2.9
